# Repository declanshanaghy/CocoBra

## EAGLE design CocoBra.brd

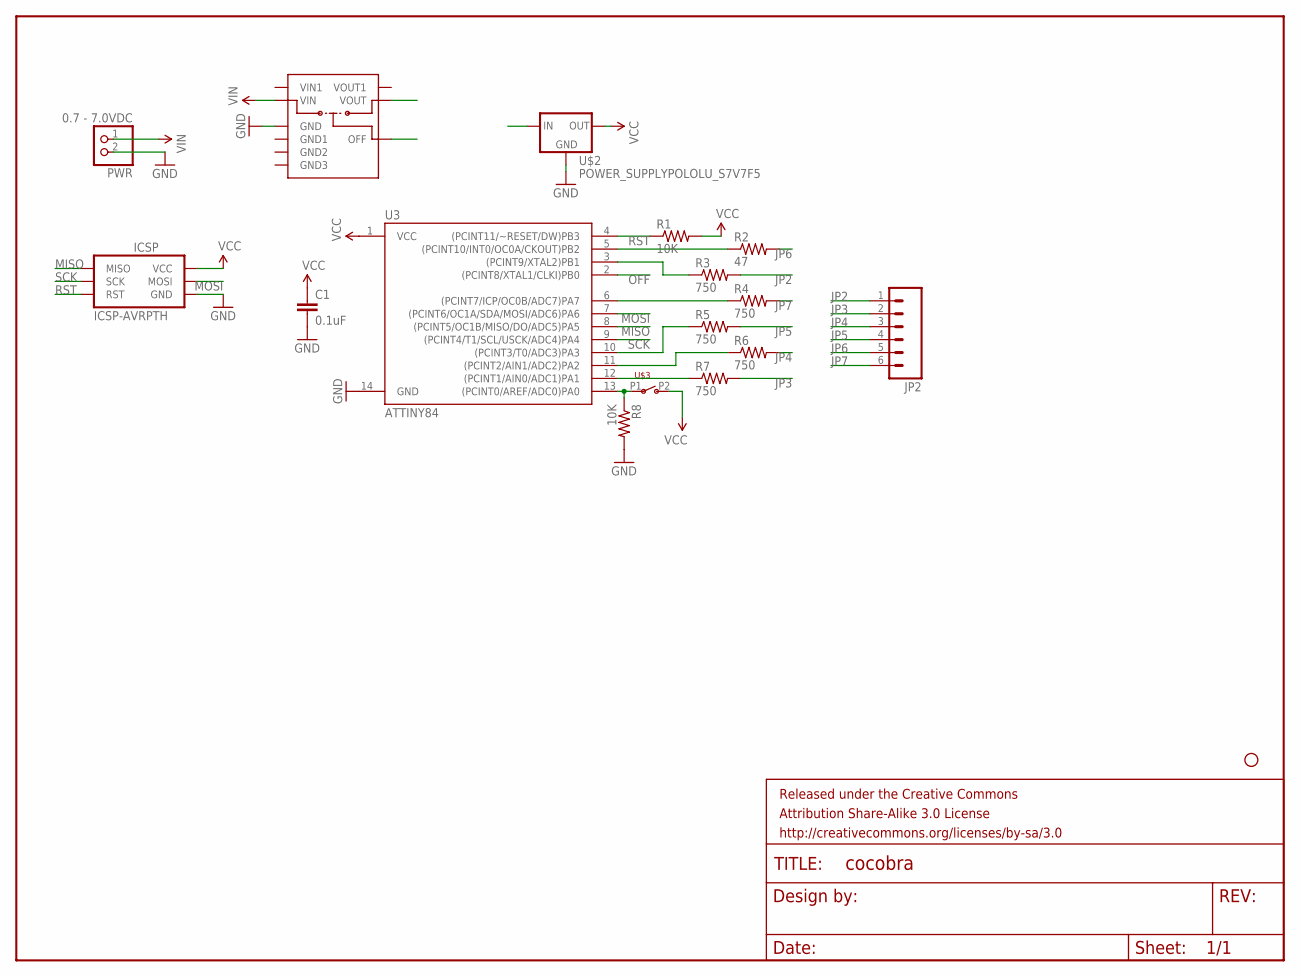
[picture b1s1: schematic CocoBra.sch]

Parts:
C1: 0.1uF; CAP-PTH-SMALL2
FRAME1: FRAME-LETTER; CREATIVE_COMMONS
ICSP: ICSP-AVRPTH; 2X3-SHROUDED
JP2: M06SIP; 1X06
PWR: 0.7 - 7.0VDC; JST-PH-2-THM-RA
R1, R8: 10K; AXIAL-0.2
R2: 47; AXIAL-0.3
R3, R4, R5, R6, R7: 750; AXIAL-0.3
STANDOFF3: STAND-OFF#2; STAND-OFF-#2
U3: ATTINY84; DIL14
U$2: POWER_SUPPLYPOLOLU_S7V7F5; POLOLU_POWER_SUPPLY_S7V7F5
U$3: SWITCH-SPSTTILT; SWITCH-SPST-TILT
U$4: POLOLU_POWER_SWITCHPTH; POLOLU_POWER_SWITCH

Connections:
GND: C1.2, ICSP.6 (GND), PWR.2 (1), R8.P$2 (2), U3.14 (GND), U$2.GND, U$4.GND
JP2: JP2.1, R3.P$2 (2)
JP3: JP2.2, R7.P$2 (2)
JP4: JP2.3, R6.P$2 (2)
JP5: JP2.4, R5.P$2 (2)
JP6: JP2.5, R2.P$2 (2)
JP7: JP2.6, R4.P$2 (2)
MISO: ICSP.1 (MISO), U3.8 ((PCINT5/OC1B/MISO/DO/ADC5)PA5)
MOSI: ICSP.4 (MOSI), U3.7 ((PCINT6/OC1A/SDA/MOSI/ADC6)PA6)
unnamed: R2.P$1 (1), U3.5 ((PCINT10/INT0/OC0A/CKOUT)PB2)
unnamed: R3.P$1 (1), U3.3 ((PCINT9/XTAL2)PB1)
unnamed: R4.P$1 (1), U3.6 ((PCINT7/ICP/OC0B/ADC7)PA7)
unnamed: R5.P$1 (1), U3.10 ((PCINT3/T0/ADC3)PA3)
unnamed: R6.P$1 (1), U3.11 ((PCINT2/AIN1/ADC2)PA2)
unnamed: R7.P$1 (1), U3.12 ((PCINT1/AIN0/ADC1)PA1)
unnamed: R8.P$1 (1), U3.13 ((PCINT0/AREF/ADC0)PA0), U$3.P1
OFF: U3.2 ((PCINT8/XTAL1/CLKI)PB0), U$4.OFF
RST: ICSP.5 (RST), R1.P$1 (1), U3.4 ((PCINT11/~RESET/DW)PB3)
SCK: ICSP.3 (SCK), U3.9 ((PCINT4/T1/SCL/USCK/ADC4)PA4)
VCC: C1.1, ICSP.2 (VCC), R1.P$2 (2), U3.1 (VCC), U$2.VOUT (OUT), U$3.P2
VIN: PWR.1 (2), U$4.VIN
VOUT: U$2.VIN (IN), U$4.VOUT

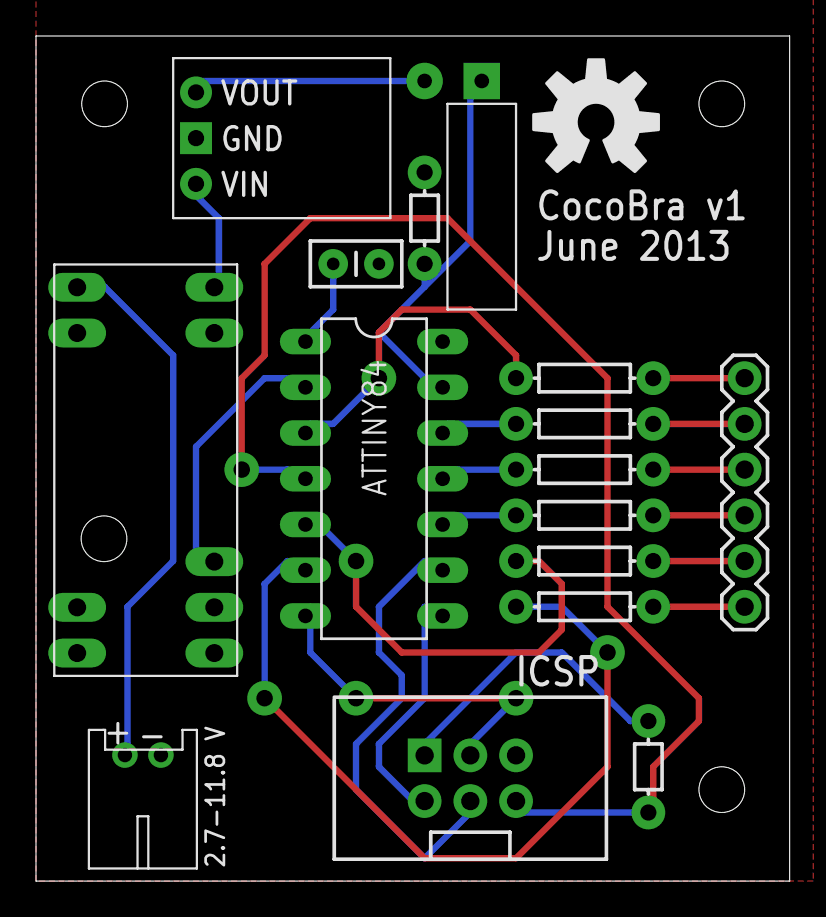
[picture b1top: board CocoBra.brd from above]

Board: 2 copper layers, 41.9 x 46.9 mm, 22 parts (0 on the bottom side), 22 nets.

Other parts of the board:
STANDOFF1, STANDOFF2, STANDOFF4: STAND-OFF#2; STAND-OFF-#2
U$1: OSHW-LOGO-L

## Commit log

2013-05-30 Added tilt switch. EagleUp model taking shape
2013-06-04 Exported static docs
2013-06-07 tagged v1
2013-06-07 Code working with v1

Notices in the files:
parts and their libraries:
SparkFun-Connectors: Licensing: CC v3.0 Share-Alike You are welcome to use this library for commercial purposes.
SparkFun-Aesthetics: Released under the Creative Commons Attribution Share-Alike 3.0 License
SparkFun-Aesthetics: http://creativecommons.org/licenses/by-sa/3.0
